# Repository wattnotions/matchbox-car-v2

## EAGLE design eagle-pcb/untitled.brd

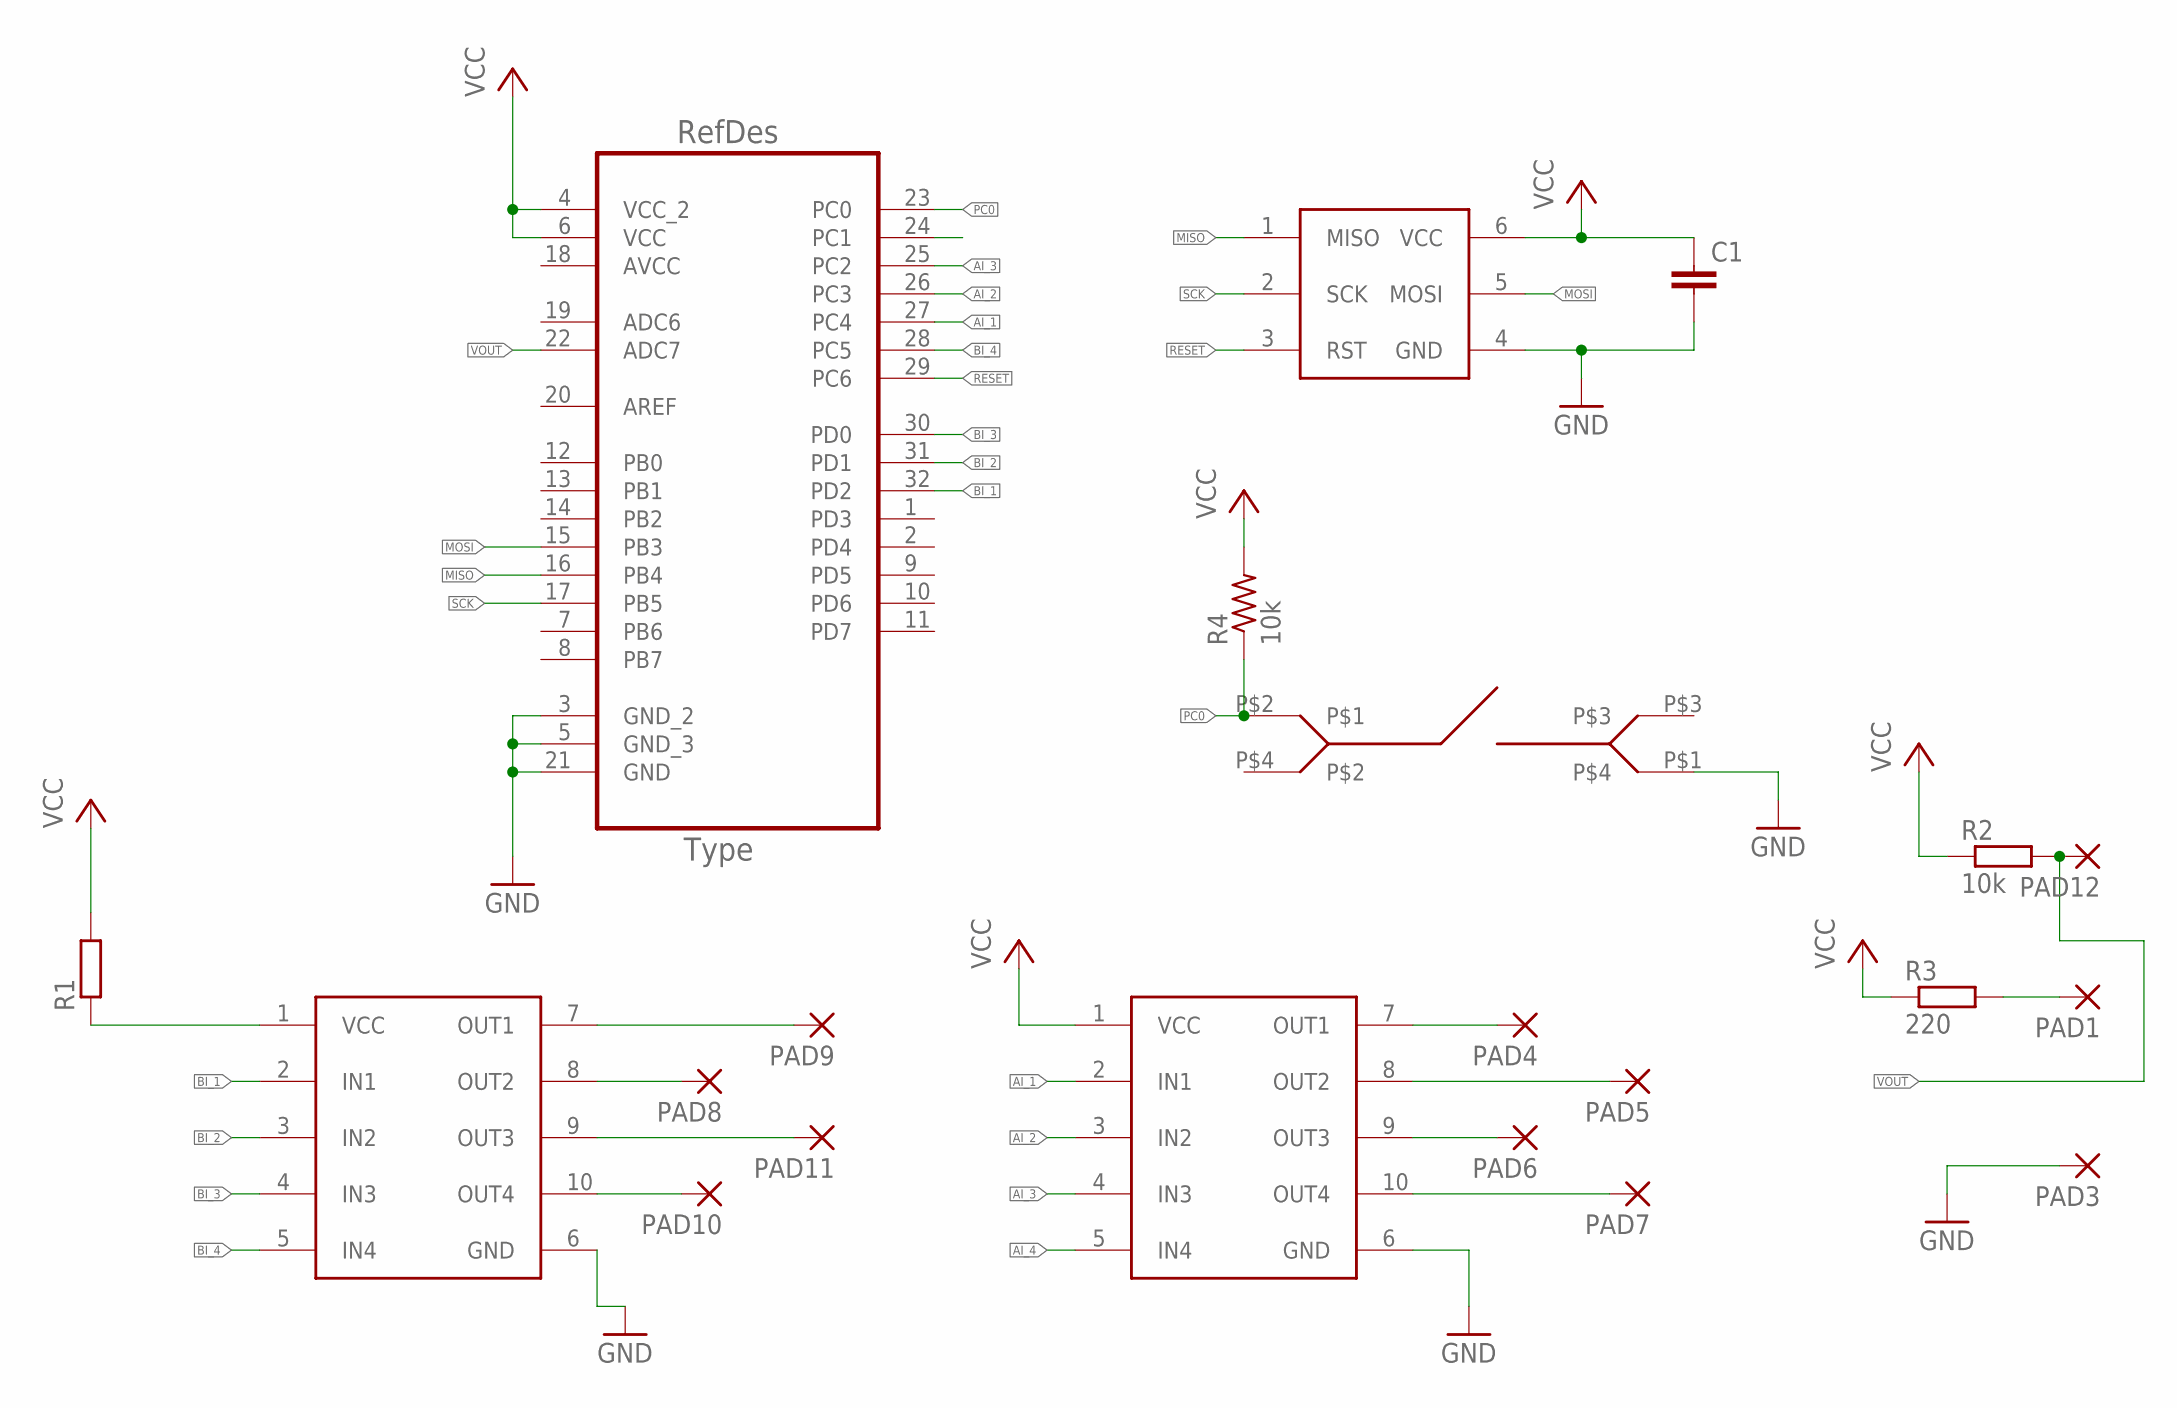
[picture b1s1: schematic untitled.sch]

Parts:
C1: CC1206; C1206
PAD1, PAD3, PAD4, PAD5, PAD6, PAD7, PAD8, PAD9, PAD10, PAD11, PAD12: SMD2; SMD1,27-2,54
R1: R-EU_M1206; M1206
R2, R4: 10k; M0805
R3: 220; M0805
U1: ATMEGA328P-AU; QFP80P900X900X120-32N
U$1, U$2: LB1948MC_STEP_DRIVE; SOIC_10
U$3: 2X6_AVR_HEADER; 2X6_AVR_PIN_HEADER_SMD
U$4: SMD_TACTILE_SWITCH; SMD_TACTILE

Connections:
AI_1: U1.27 (PC4), U$2.2 (IN1)
AI_2: U1.26 (PC3), U$2.3 (IN2)
AI_3: U1.25 (PC2), U$2.4 (IN3)
AI_4: U1.24 (PC1), U$2.5 (IN4)
AVCC: U1.18 (AVCC)
BI_1: U1.32 (PD2), U$1.2 (IN1)
BI_2: U1.31 (PD1), U$1.3 (IN2)
BI_3: U1.30 (PD0), U$1.4 (IN3)
BI_4: U1.28 (PC5), U$1.5 (IN4)
GND: C1.2, PAD3.1, U1.3 (GND_2), U1.5 (GND_3), U1.21 (GND), U$1.6 (GND), U$2.6 (GND), U$3.4 (GND), U$4.P$1
MISO: U1.16 (PB4), U$3.1 (MISO)
MOSI: U1.15 (PB3), U$3.5 (MOSI)
unnamed: PAD4.1, U$2.7 (OUT1)
unnamed: PAD5.1, U$2.8 (OUT2)
unnamed: PAD6.1, U$2.9 (OUT3)
unnamed: PAD7.1, U$2.10 (OUT4)
unnamed: PAD9.1, U$1.7 (OUT1)
unnamed: PAD8.1, U$1.8 (OUT2)
unnamed: PAD11.1, U$1.9 (OUT3)
unnamed: PAD10.1, U$1.10 (OUT4)
unnamed: R1.1, U$1.1 (VCC)
unnamed: PAD1.1, R3.2
PC0: R4.1, U1.23 (PC0), U$4.P$2
RESET: U1.29 (PC6), U$3.3 (RST)
SCK: U1.17 (PB5), U$3.2 (SCK)
VCC: C1.1, R1.2, R2.1, R3.1, R4.2, U1.4 (VCC_2), U1.6 (VCC), U$2.1 (VCC), U$3.6 (VCC)
VOUT: PAD12.1, R2.2, U1.22 (ADC7)

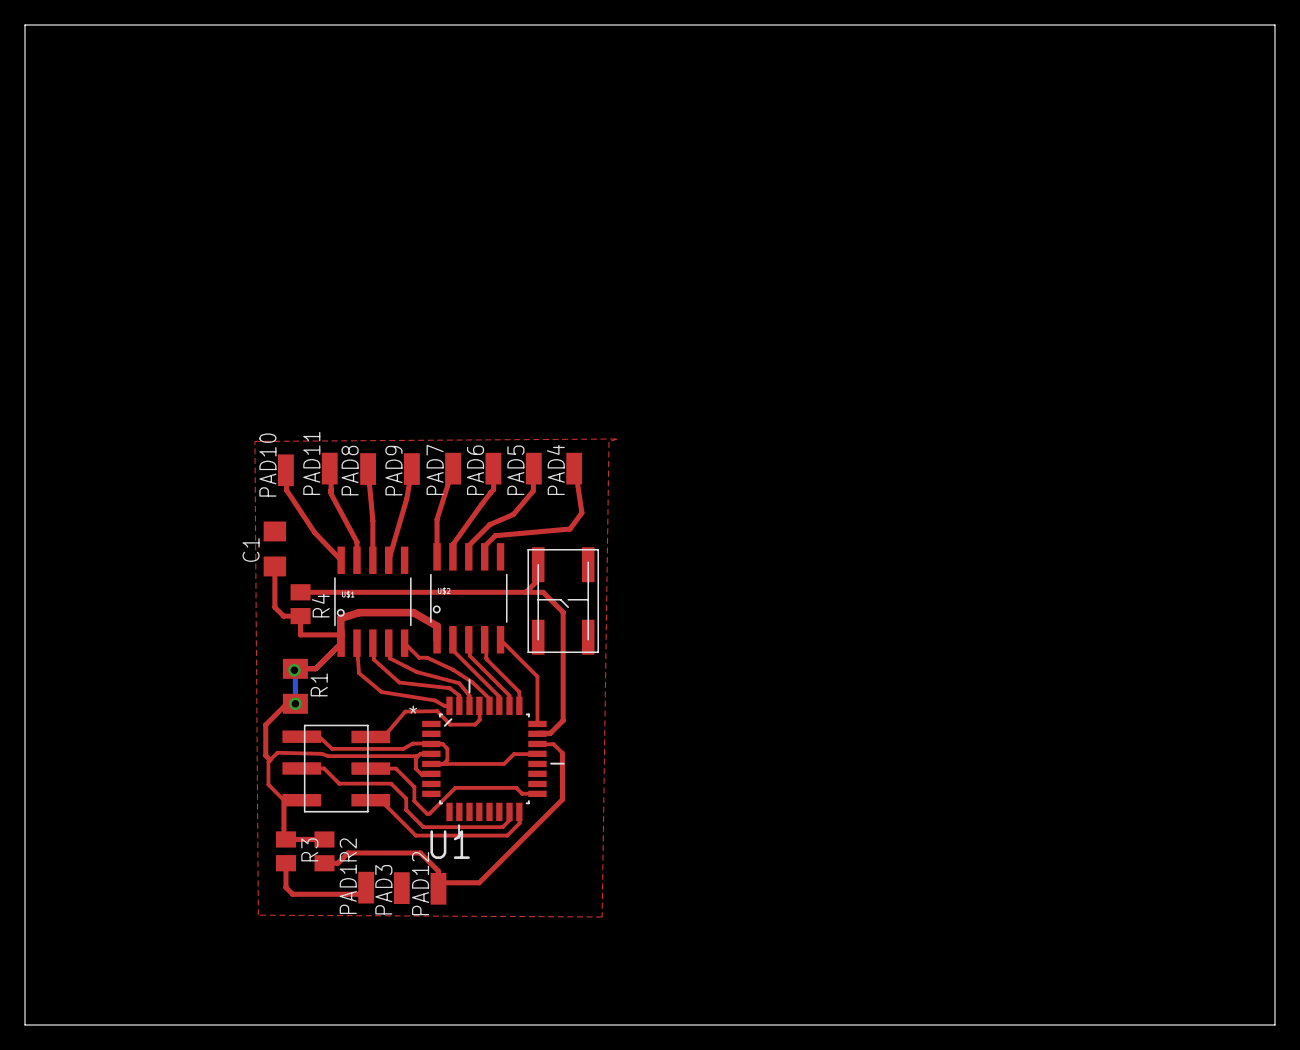
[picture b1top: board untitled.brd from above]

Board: 2 copper layers, 100.0 x 80.0 mm, 21 parts (0 on the bottom side), 26 nets.

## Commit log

2015-09-11 :octocat: Added .gitattributes & .gitignore files
2015-09-11 eagle pcb files
2015-09-11 added pdf of circuit diagram
2015-09-11 pcb artwork for etching
